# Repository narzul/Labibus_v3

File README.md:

Labibus_v3

Ref: https://labitat.dk/wiki/Labibus

price components around: 12 EUR
can be cheaper in bulk

|Reference          |Quantity|Value                        |Price |
|-------------------|--------|-----------------------------|------|
|C1 C3 C4 C9 C10    |5       |10uF                         |0.5   |
|C2 C5 C6 C7 C8 C11 |6       |0.1uF                        |0.6   |
|D1 D2 D3 D4        |4       |LED                          |0.4   |
|J1                 |1       |Screw_Terminal_01x04         |0.992 |
|J2                 |1       |Conn_01x16                   |0.992 |
|J3                 |1       |Conn_01x06                   |0.372 |
|J4                 |1       |Conn_01x03                   |0.186 |
|J5                 |1       |Conn_01x15                   |0.93  |
|J6                 |1       |Conn_01x12                   |0.744 |
|J7                 |1       |Conn_01x04 Qwiic JST SH 4-pin|0.5   |
|JP1 JP2            |2       |SolderJumper_2_Open          |0     |
|R10 R11            |2       |10k                          |0.2   |
|R1 R2 R12          |3       |1k                           |0.3   |
|R3 R4              |2       |20k                          |0.2   |
|R5                 |1       |120                          |0.1   |
|R6                 |1       |100k                         |0.1   |
|R7                 |1       |300                          |0.1   |
|RN1                |1       |10k                          |0.09  |
|SW1                |1       |SW_Push                      |0.123 |
|U1                 |1       |MIC5205-5.0YM5               |0.455 |
|U2                 |1       |MAX485E                      |2.62  |
|U3                 |1       |ATmega328P-AU                |2.21  |
|U4                 |1       |MIC5219-3.3YM5               |0.455 |
|Y1                 |1       |Crystal_GND2_Small           |0.245 |
|                   |        |                             |13.414|

1. Update the difference protocolls
2. Install in the bunker, with sensors
3. make a case
4. Do workshop

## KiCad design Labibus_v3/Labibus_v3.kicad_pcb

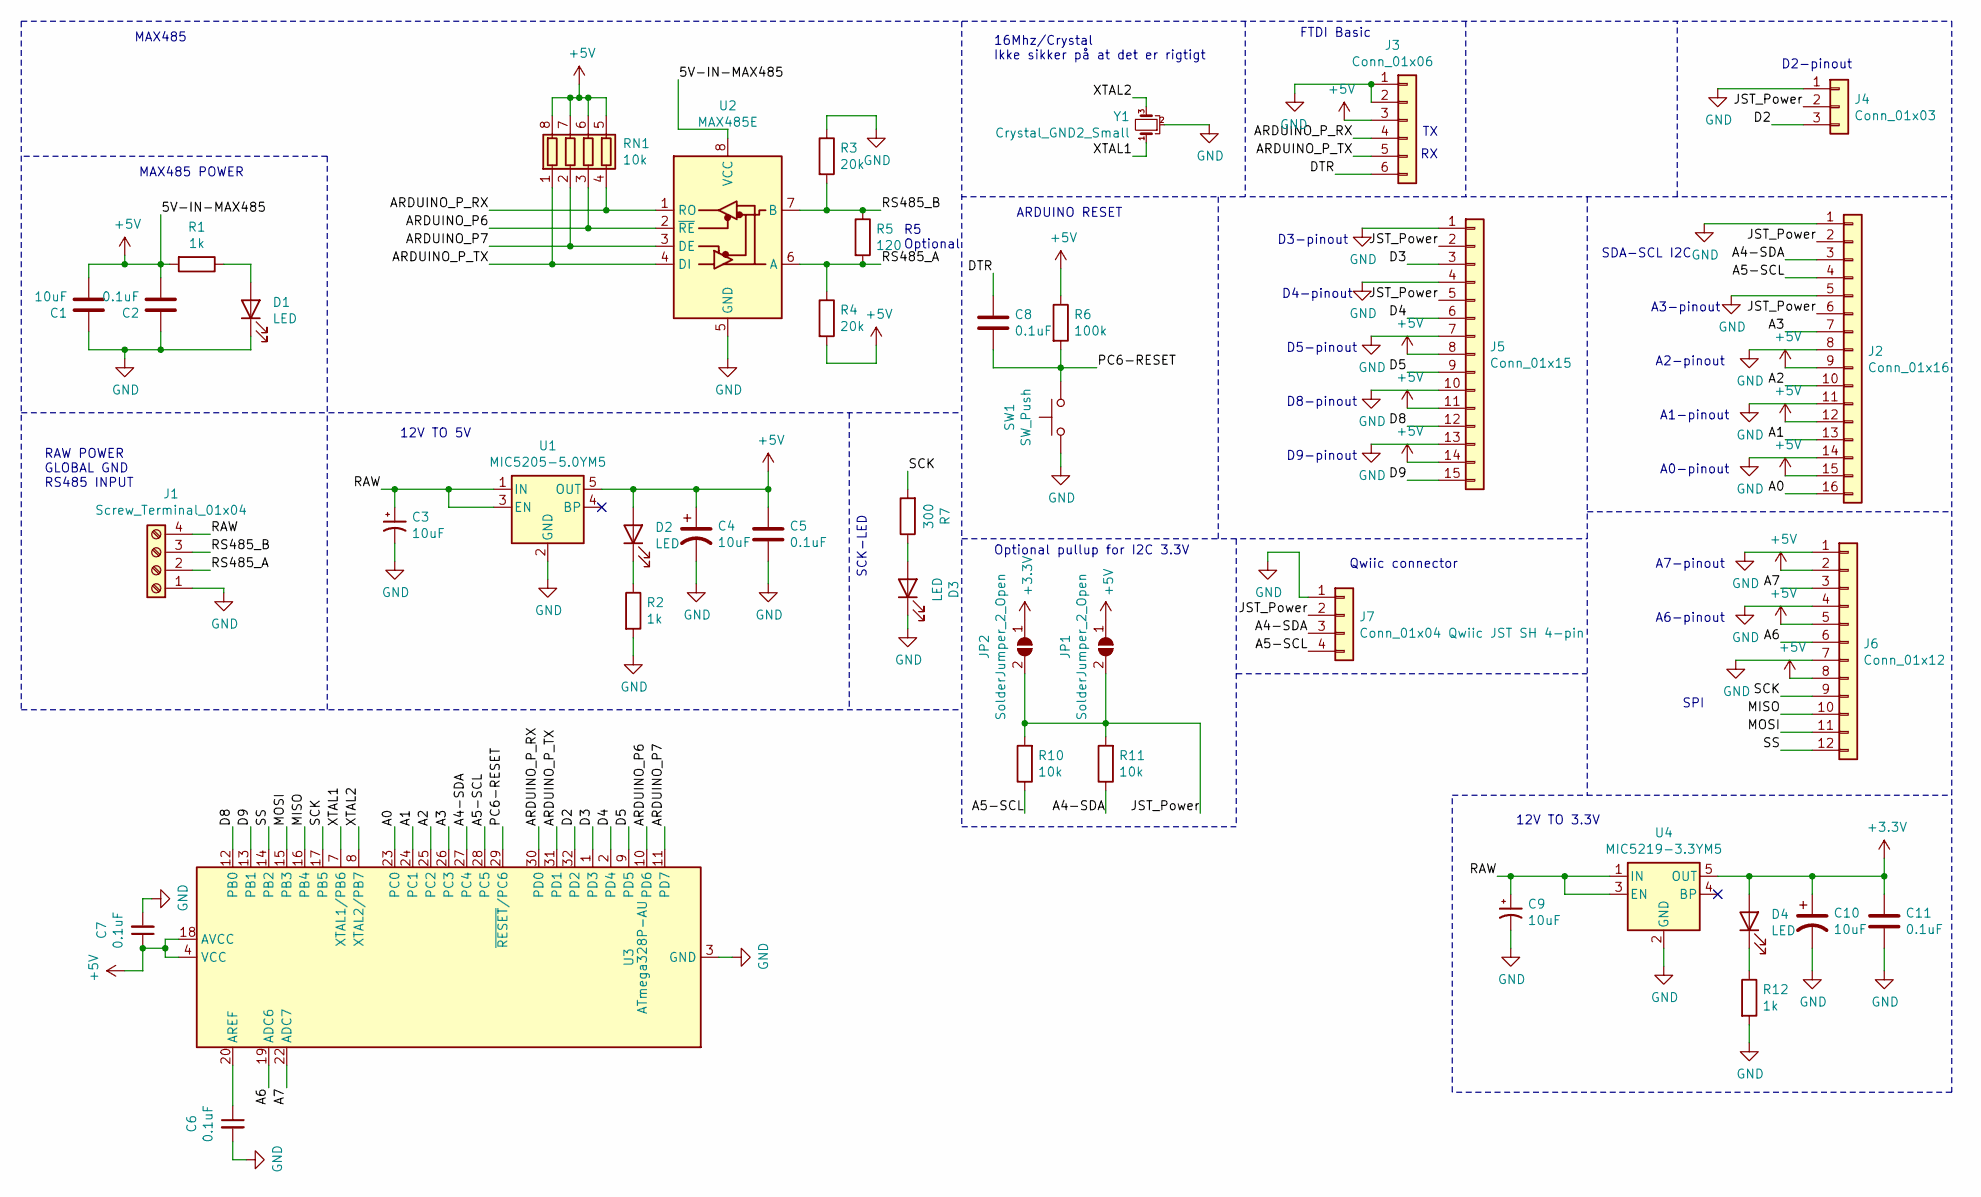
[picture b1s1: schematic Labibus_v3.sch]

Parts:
C1, C3, C4, C9, C10: 10uF; C_0603_1608Metric_Pad1.08x0.95mm_HandSolder
C2, C5, C6, C7, C8, C11: 0.1uF; C_0603_1608Metric_Pad1.08x0.95mm_HandSolder
D1, D2, D3, D4: LED; LED_0603_1608Metric_Pad1.05x0.95mm_HandSolder
J1: Screw_Terminal_01x04; TerminalBlock_Phoenix_MPT-0,5-4-2.54_1x04_P2.54mm_Horizontal
J2: Conn_01x16; PinSocket_1x16_P2.54mm_Vertical
J3: Conn_01x06; PinHeader_1x06_P2.54mm_Vertical
J4: Conn_01x03; PinSocket_1x03_P2.54mm_Vertical
J5: Conn_01x15; PinSocket_1x15_P2.54mm_Vertical
J6: Conn_01x12; PinSocket_1x12_P2.54mm_Vertical
J7: Conn_01x04 Qwiic JST SH 4-pin; JST_SH_BM04B-SRSS-TB_1x04-1MP_P1.00mm_Vertical
JP1, JP2: SolderJumper_2_Open; SolderJumper-2_P1.3mm_Open_RoundedPad1.0x1.5mm
R1, R2, R12: 1k; R_0603_1608Metric_Pad0.98x0.95mm_HandSolder
R3, R4: 20k; R_0603_1608Metric_Pad0.98x0.95mm_HandSolder
R5: 120; R_0603_1608Metric_Pad0.98x0.95mm_HandSolder
R6: 100k; R_0603_1608Metric_Pad0.98x0.95mm_HandSolder
R7: 300; R_0603_1608Metric_Pad0.98x0.95mm_HandSolder
R10, R11: 10k; R_0603_1608Metric_Pad0.98x0.95mm_HandSolder
RN1: 10k; R_Array_Concave_4x0603
SW1: SW_Push; SW_SPST_EVQPE1
U1: MIC5205-5.0YM5; SOT-23-5
U2: MAX485E; SOIC-8_3.9x4.9mm_P1.27mm
U3: ATmega328P-AU; TQFP-32_7x7mm_P0.8mm
U4: MIC5219-3.3YM5; SOT-23-5
Y1: Crystal_GND2_Small; Resonator_SMD_muRata_CSTxExxV-3Pin_3.0x1.1mm_HandSoldering

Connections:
+3V3: C10.1, C11.1, D4.2 (A), JP2.1 (A), U4.5 (OUT)
+5V: C1.2, C2.2, C4.1, C5.1, C7.1, D2.2 (A), J2.9, J2.12, J2.15, J3.3, J5.8, J5.11, J5.14, J6.2, J6.5, J6.8, JP1.1 (A), R1.2, R4.2, R6.1, RN1.5 (R4.2), RN1.6 (R3.2), RN1.7 (R2.2), RN1.8 (R1.2), U1.5 (OUT), U2.8 (VCC), U3.4 (VCC), U3.6 (VCC), U3.18 (AVCC)
/A0: J2.16, U3.23 (PC0)
/A1: J2.13, U3.24 (PC1)
/A2: J2.10, U3.25 (PC2)
/A3: J2.7, U3.26 (PC3)
/A4-SDA: J2.3, J7.3, R11.1, U3.27 (PC4)
/A5-SCL: J2.4, J7.4, R10.1, U3.28 (PC5)
/A6: J6.6, U3.19 (ADC6)
/A7: J6.3, U3.22 (ADC7)
/ARDUINO_P6: RN1.3 (R3.1), U2.2 (~RE), U3.10 (PD6)
/ARDUINO_P7: RN1.2 (R2.1), U2.3 (DE), U3.11 (PD7)
/ARDUINO_P_RX: J3.4, RN1.4 (R4.1), U2.1 (RO), U3.30 (PD0)
/ARDUINO_P_TX: J3.5, RN1.1 (R1.1), U2.4 (DI), U3.31 (PD1)
/D2: J4.3, U3.32 (PD2)
/D3: J5.3, U3.1 (PD3)
/D4: J5.6, U3.2 (PD4)
/D5: J5.9, U3.9 (PD5)
/D8: J5.12, U3.12 (PB0)
/D9: J5.15, U3.13 (PB1)
/DTR: C8.2, J3.6
/JST_Power: J2.2, J2.6, J4.2, J5.2, J5.5, J7.2, JP1.2 (B), JP2.2 (B), R10.2, R11.2
/MISO: J6.10, U3.16 (PB4)
/MOSI: J6.11, U3.15 (PB3)
/PC6-RESET: C8.1, R6.2, SW1.2, U3.29 (~RESET~/PC6)
/RAW: C3.1, C9.1, J1.4, U1.1 (IN), U1.3 (EN), U4.1 (IN), U4.3 (EN)
/RS485_A: J1.2, R4.1, R5.2, U2.6 (A)
/RS485_B: J1.3, R3.2, R5.1, U2.7 (B)
/SCK: J6.9, R7.2, U3.17 (PB5)
/SS: J6.12, U3.14 (PB2)
/XTAL1: U3.7 (XTAL1/PB6), Y1.1
/XTAL2: U3.8 (XTAL2/PB7), Y1.3
GND: C1.1, C2.1, C3.2, C4.2, C5.2, C6.2, C7.2, C9.2, C10.2, C11.2, D1.1 (K), D3.1 (K), J1.1, J2.1, J2.5, J2.8, J2.11, J2.14, J3.1, J3.2, J4.1, J5.1, J5.4, J5.7, J5.10, J5.13, J6.1, J6.4, J6.7, J7.1, R2.2, R3.1, R12.2, SW1.1, U1.2 (GND), U2.5 (GND), U3.3 (GND), U3.5 (GND), U3.21 (GND), U4.2 (GND), Y1.2
unnamed: C6.1, U3.20 (AREF)
unnamed: D1.2 (A), R1.1
unnamed: D2.1 (K), R2.1
unnamed: D3.2 (A), R7.1
unnamed: D4.1 (K), R12.1

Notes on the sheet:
16Mhz/Crystal Ikke sikker på at det er rigtigt
MAX485
MAX485 POWER
RAW POWER GLOBAL GND RS485 INPUT
12V TO 5V
FTDI Basic
SPI
ARDUINO RESET
SCK-LED
D3-pinout
D2-pinout
D5-pinout
D4-pinout
D8-pinout
D9-pinout
A6-pinout
A7-pinout
A0-pinout
SDA-SCL I2C
A1-pinout
A2-pinout
A3-pinout
R5 Optional
12V TO 3.3V
Optional pullup for I2C 3.3V
Qwiic connector

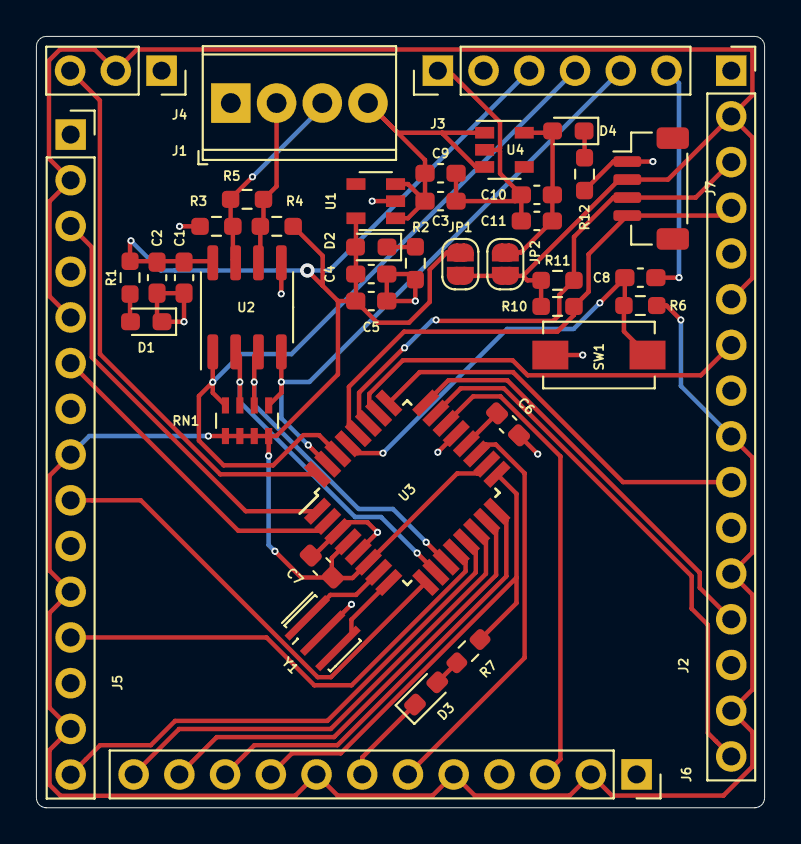
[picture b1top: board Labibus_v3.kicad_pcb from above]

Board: 2 copper layers, 40.5 x 42.9 mm, 41 parts (0 on the bottom side), 38 nets.

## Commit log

2021-12-03 start
2021-12-03 Start some datasheet added. -More needs to be added Started om sch and almost done.
2021-12-09 update started on first pcb layout
2021-12-11 new update to the pcb layout Note: Change pin row to 13 on the left side to shrink the size
2021-12-11 added tabel and price. board version 1.2
2021-12-11 update to csv and readme
2021-12-11 update to readme
2021-12-11 added pic to readme
2021-12-11 changde me to md
2021-12-11 update to picture
2021-12-11 update to PCB, layout update.
2021-12-16 update to the pcb. 3v3 added I2C 3.3 and 5 JST added.
2021-12-16 testing i can commit, i have commitment issues
2021-12-16 new branch test
2021-12-16 update with: 3.3V and 5V select JST connector
2021-12-16 simple update
